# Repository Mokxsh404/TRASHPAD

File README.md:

# TRASHPAD ⌨️

a macropad i built because i was tired of reaching for shortcuts that don't exist. got out of hand. zero regrets.

## what is this

TRASHPAD is a custom programmable macropad — 9 keys, a rotary encoder, and a tiny OLED screen that actually tells you what's going on. built it for a hackathon and then kept going way past the point where "good enough" would've been fine. ended up with a full custom PCB, a 3D-printable case, and a website to go with it.

👉 **[try the interactive demo](https://mokxsh404.github.io/TRASHPAD/)**

## what's inside

🔘 **9 programmable keys** — fully remappable through a QMK firmware matrix. bind them to whatever you actually use, not whatever the factory default thinks you need.

🎛️ **EC11 rotary encoder** — volume, scrubbing, scrolling through a timeline, whatever. smooth, satisfying, and somehow the part everyone immediately gravitates to when they pick it up.

📟 **0.91" OLED display** — shows live layer state and active macros so you're not just guessing what your own keyboard is doing. small detail, makes the whole thing feel like a real device instead of a breadboard with delusions of grandeur.

🧠 **XIAO RP2040** — tiny controller, does all the heavy lifting, somehow still cheaper than a fancy keycap set.

## where it's at

PCB is designed, firmware is configured, and the production files (gerbers included) are ready to send to a fab. case is modeled and exported. basically: this thing exists in CAD and code, and the build/test phase is where it's at right now.

## the build

**schematic**

**PCB**

**CAD model**

## bill of materials (bom)

Here is everything you need to source to build your own TRASHPAD. All parts are standard and easy to find on sites like AliExpress, Amazon, or specialized keyboard vendors.

| Component | Description | Qty | Est. Cost | Notes |
| :--- | :--- | :---: | :---: | :--- |
| **Seeed Studio XIAO RP2040** | Dual-core Cortex-M0+ microcontroller, USB-C | 1 | ~$5.50 | Main controller footprint |
| **0.91" I2C OLED Display** | SSD1306, 128x32 screen | 1 | ~$3.00 | 4-pin header connection |
| **EC11 Rotary Encoder** | EC11 encoder with push-button switch, D-shaft (15mm) | 1 | ~$1.50 | 5-pin footprint |
| **Keyswitches** | Cherry MX-compatible switches (Gateron, Kailh, etc.) | 9 | ~$4.00 | Soldered directly to PCB |
| **1u Keycaps** | MX-style keycaps | 9 | ~$3.00 | Standard 1u size |
| **1N4148 Diodes** | Switching diodes | 9 | ~$0.50 | SOD-123 surface mount |
| **TRASHPAD Custom PCB** | Custom printed circuit board (Fab & Shipping) | 1 | ~$6.00 | JLCPCB/PCBWay fab + shipping share |
| **3D Printed Case & Knob** | Top casing, bottom plate, and encoder knob | 1 | ~$5.00 | Using local hub / custom printing service |
| **M3 Threaded Inserts** | Brass heat-set inserts | 4 | ~$0.50 | Ø 4.7mm × 4.0mm inserts |
| **M3 Machine Screws** | M3 screws for case | 4 | ~$0.50 | M3 × 6mm or 8mm button-head |
| **Rubber Feet** | Self-adhesive silicone bumpers | 4 | ~$0.50 | Ø 8mm x 2mm feet |
| **Total Build Cost** | | | **~$30.00** | *(Excludes tools, shipping, USB-C)* |

## repo structure

- `CAD/` — full assembled model for reference (`assembled-model.step`)
- `docs/` — the interactive site/simulator, this is what's live on GitHub Pages
- `Frimware/` — QMK config: keymaps, `config.h`, `keyboard.json`, `rules.mk`
- `PCB/` — KiCad project, schematic, and PCB layout files
- `Production/` — fab-ready output: gerbers, case STEPs (`Top.step`, `Bottom.step`), and the `trashpad/` build folder

## stack

KiCad for the PCB, QMK for firmware, plain HTML/CSS/JS for the site — no frameworks, no build step, just files that work.

## resources that actually helped

- [ai03's PCB guide](https://wiki.ai03.com/) — if you've never routed a board before, start here
- [the keyboard designer wiki](https://wiki.keyboardatelier.com/)
- [Joe Scotto's case tutorials](https://www.youtube.com/watch?v=33mCOnFioY0)

## about

I wanted a macropad.

Instead of buying one, I spent days learning PCB design, designing a case in Fusion, configuring firmware, and making a website for it.

TRASHPAD is the result.

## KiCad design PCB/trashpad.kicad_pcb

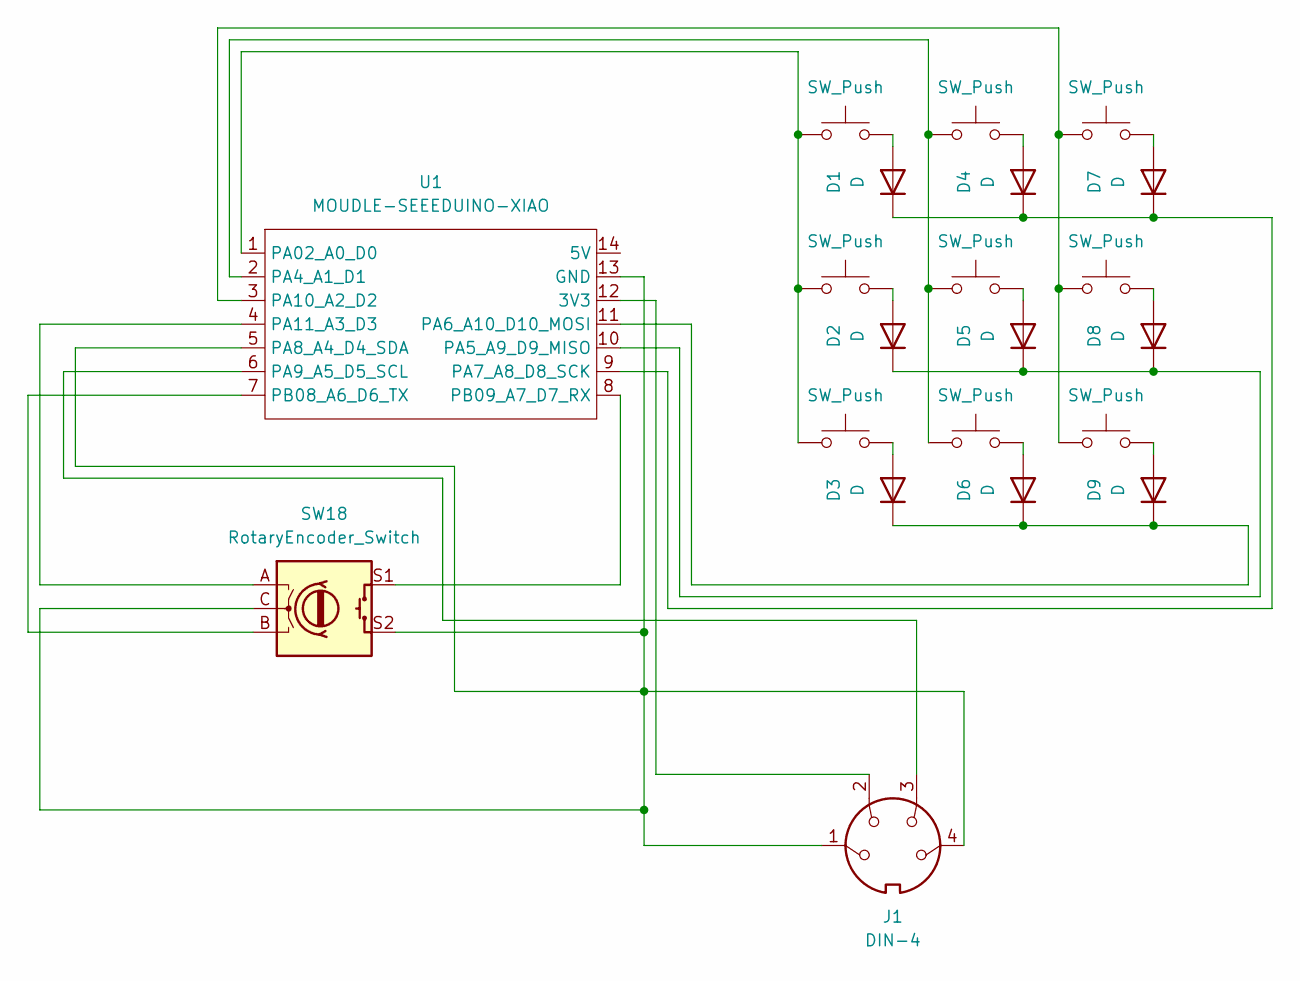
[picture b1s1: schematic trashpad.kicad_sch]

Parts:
D1, D2, D3, D4, D5, D6, D7, D8, D9: D; D_DO-35_SOD27_P7.62mm_Horizontal
J1: DIN-4; SSD1306-0.91-OLED-4pin-128x32
SW1, SW2, SW3, SW4, SW5, SW6, SW7, SW8, SW9: SW_Push; SW_Cherry_MX_1.00u_PCB
SW18: RotaryEncoder_Switch; RotaryEncoder_Alps_EC11E-Switch_Vertical_H20mm
U1: MOUDLE-SEEEDUINO-XIAO; XIAO-Generic-Hybrid-14P-2.54-21X17.8MM

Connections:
unnamed: D1.2 (A), SW1.2
unnamed: D1.1 (K), D4.1 (K), D7.1 (K), U1.9 (PA7_A8_D8_SCK)
unnamed: D2.2 (A), SW2.2
unnamed: D2.1 (K), D5.1 (K), D8.1 (K), U1.10 (PA5_A9_D9_MISO)
unnamed: D3.2 (A), SW3.2
unnamed: D3.1 (K), D6.1 (K), D9.1 (K), U1.11 (PA6_A10_D10_MOSI)
unnamed: D4.2 (A), SW4.2
unnamed: D5.2 (A), SW5.2
unnamed: D6.2 (A), SW6.2
unnamed: D7.2 (A), SW7.2
unnamed: D8.2 (A), SW8.2
unnamed: D9.2 (A), SW9.2
unnamed: J1.2, U1.12 (3V3)
unnamed: J1.1, J1.4, SW18.C, SW18.S2, U1.5 (PA8_A4_D4_SDA), U1.13 (GND)
unnamed: SW1.1, SW2.1, SW3.1, U1.1 (PA02_A0_D0)
unnamed: SW4.1, SW5.1, SW6.1, U1.2 (PA4_A1_D1)
unnamed: J1.3, U1.6 (PA9_A5_D5_SCL)
unnamed: SW7.1, SW8.1, SW9.1, U1.3 (PA10_A2_D2)
unnamed: SW18.A, U1.4 (PA11_A3_D3)
unnamed: SW18.B, U1.7 (PB08_A6_D6_TX)
unnamed: SW18.S1, U1.8 (PB09_A7_D7_RX)

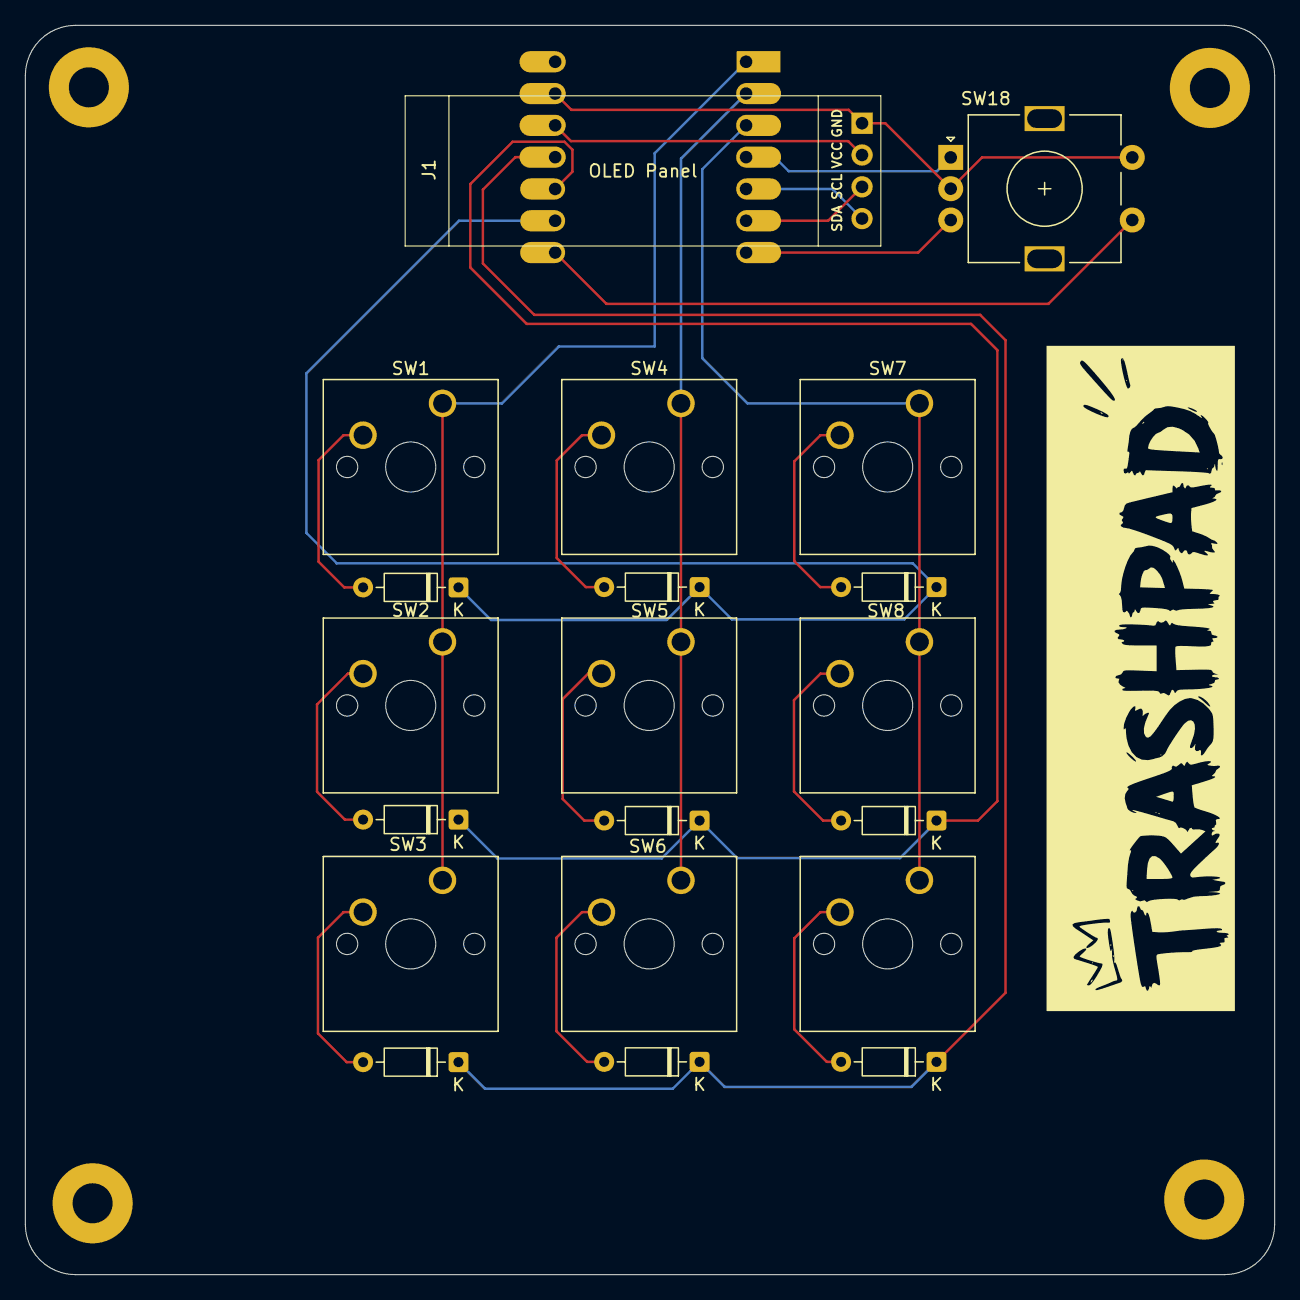
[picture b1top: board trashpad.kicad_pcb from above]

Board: 2 copper layers, 99.8 x 99.8 mm, 21 parts (1 on the bottom side), 21 nets.

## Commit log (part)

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2026-06-24 Update CAD files and 3D model assets
2026-06-25 bom edit
